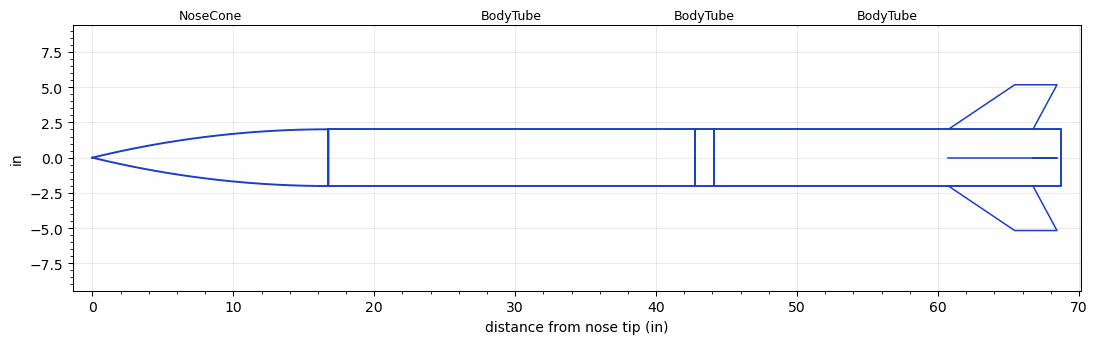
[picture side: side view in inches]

<RASAeroDocument>
 <FileVersion>2</FileVersion>
 <RocketDesign>
  <NoseCone>
   <Length>16.75</Length>
   <Diameter>4.024</Diameter>
   <Shape>Tangent Ogive</Shape>
   <Location>0</Location>
  </NoseCone>
  <BodyTube>
   <Length>26</Length>
   <Diameter>4.024</Diameter>
   <Location>16.75</Location>
  </BodyTube>
  <BodyTube>
   <Length>1.33</Length>
   <Diameter>4.024</Diameter>
   <Location>42.75</Location>
  </BodyTube>
  <BodyTube>
   <Length>24.66</Length>
   <Diameter>4.024</Diameter>
   <Location>44.08</Location>
   <Fin>
    <Count>4</Count>
    <Chord>6</Chord>
    <Span>3.16</Span>
    <SweepDistance>4.703</SweepDistance>
    <TipChord>3</TipChord>
    <Thickness>0.165</Thickness>
    <Location>8</Location>
    <AirfoilSection>Square</AirfoilSection>
   </Fin>
  </BodyTube>
  <Surface>Smooth Paint</Surface>
  <ModifiedBarrowman>False</ModifiedBarrowman>
  <Turbulence>False</Turbulence>
  <UseBooster1>False</UseBooster1>
  <UseBooster2>False</UseBooster2>
 </RocketDesign>
 <LaunchSite>
  <Altitude>7</Altitude>
  <Pressure>30.16</Pressure>
  <RodAngle>0</RodAngle>
  <RodLength>5</RodLength>
  <Temperature>60</Temperature>
  <WindSpeed>0</WindSpeed>
 </LaunchSite>
 <Recovery>
  <Altitude1>1000</Altitude1>
  <Altitude2>656.168</Altitude2>
  <DeviceType1>Parachute</DeviceType1>
  <DeviceType2>Parachute</DeviceType2>
  <Event1>True</Event1>
  <Event2>True</Event2>
  <Size1>15</Size1>
  <Size2>48</Size2>
  <EventType1>Apogee</EventType1>
  <EventType2>Altitude</EventType2>
  <CD1>1.55</CD1>
  <CD2>1.55</CD2>
 </Recovery>
 <SimulationList>
  <Simulation>
   <SustainerEngine>J500G  (Aerotech)</SustainerEngine>
   <SustainerLaunchWt>9.63</SustainerLaunchWt>
   <SustainerNozzleDiameter>2.4</SustainerNozzleDiameter>
   <SustainerCG>41.5</SustainerCG>
   <SustainerIgnitionDelay>0</SustainerIgnitionDelay>
   <Booster1SeparationDelay>0</Booster1SeparationDelay>
   <Booster1IgnitionDelay>0</Booster1IgnitionDelay>
   <IncludeBooster1>False</IncludeBooster1>
   <Booster2Delay>0</Booster2Delay>
   <IncludeBooster2>False</IncludeBooster2>
   <TimetoApogee>12.8102</TimetoApogee>
   <MaxAltitude>2826.632</MaxAltitude>
   <MaxVelocity>494.346</MaxVelocity>
   <OptimumWt>4.815</OptimumWt>
   <OptimumMaxAlt>4.815</OptimumMaxAlt>
  </Simulation>
 </SimulationList>
</RASAeroDocument>
